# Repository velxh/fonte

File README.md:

# Fonte de alimentação
A fonte usa como saídas as próprias saídas da fonte, que são respectivamente de 3,3V, 5V, 12V e -12V. A parte regulável foi feita a partir de um fio em paralelo conctando a saída de 12V a um circuito com o regulador de tensão LM317 e sendo ajustável por um potenciômetro.

Esse projeto se resume basicamente em conexões e solda de fios, visto que as saídas fixas apenas tiveram seus fios conectados em plugs banana fêmeas, e o fio de 12V teve sua saída bifurcada para que um fio se conectasse em um plug banana e o outro foi soldado na PCI reguladora.

Modelo 3D idealizado:
<div align="center">

</div>

Projeto finalizado:

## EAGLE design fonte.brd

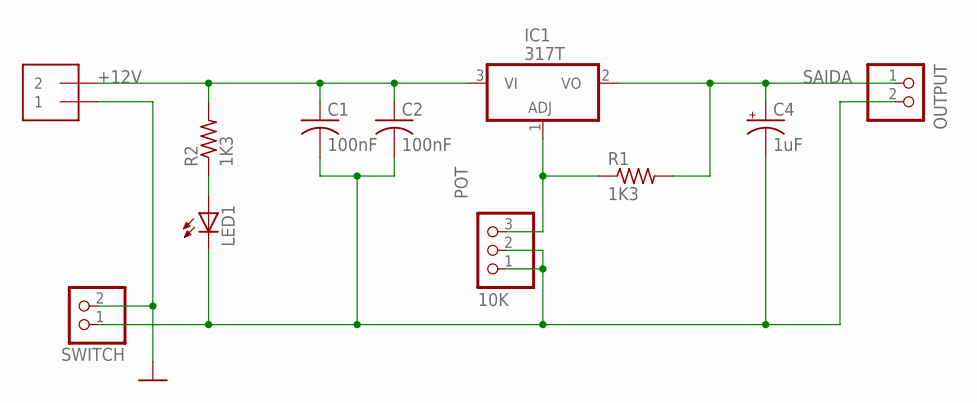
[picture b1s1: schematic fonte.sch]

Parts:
C1, C2: 100nF; C025-025X050
C4: 1uF; CPOL-RADIAL-2.5MM-5MM
IC1: 317T; TO220H
INPUT: 1X2-3.5MM
LED1: LED5MM
OUTPUT: PINHD-1X2; 1X02
POT: 10K; 1X03
R1, R2: 1K3; 0204/7
SWITCH: PINHD-1X2; 1X02

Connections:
+12V: C1.1, C2.1, IC1.3 (VI), INPUT.2, R2.2
GND: INPUT.1, SWITCH.2
unnamed: IC1.1 (ADJ), POT.3, R1.1
unnamed: LED1.A, R2.1
unnamed: C1.2, C2.2, C4.2 (-), LED1.K (C), OUTPUT.2, POT.1, POT.2, SWITCH.1
SAIDA: C4.1 (+), IC1.2 (VO), OUTPUT.1, R1.2

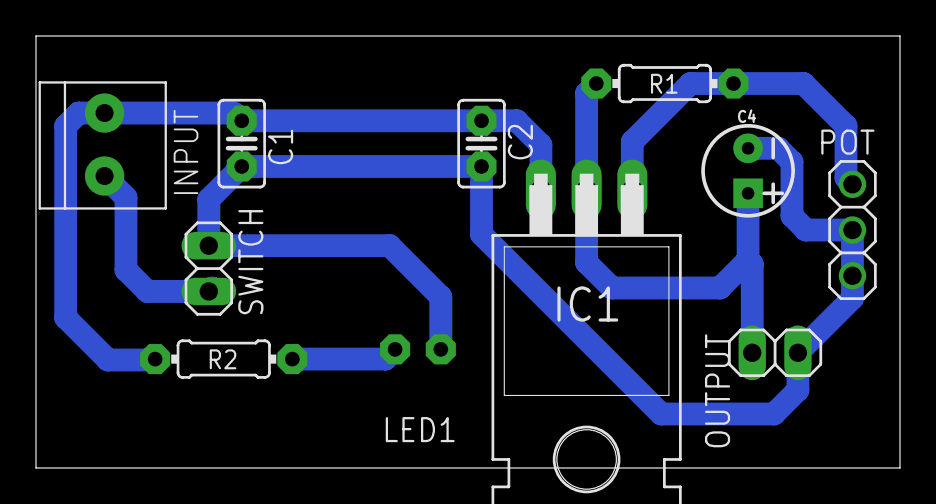
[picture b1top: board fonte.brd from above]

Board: 2 copper layers, 48.0 x 24.0 mm, 11 parts (1 on the bottom side), 6 nets.

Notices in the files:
parts and their libraries:
SparkFun-Capacitors: Licensing: Creative Commons ShareAlike 4.0 International - https://creativecommons.org/licenses/by-sa/4.0
